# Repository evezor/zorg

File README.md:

# To be named Zorg Placeholder

Zorg is the webportal to the evezor edge systems ecosystem, plus other stuff, I think... maybe

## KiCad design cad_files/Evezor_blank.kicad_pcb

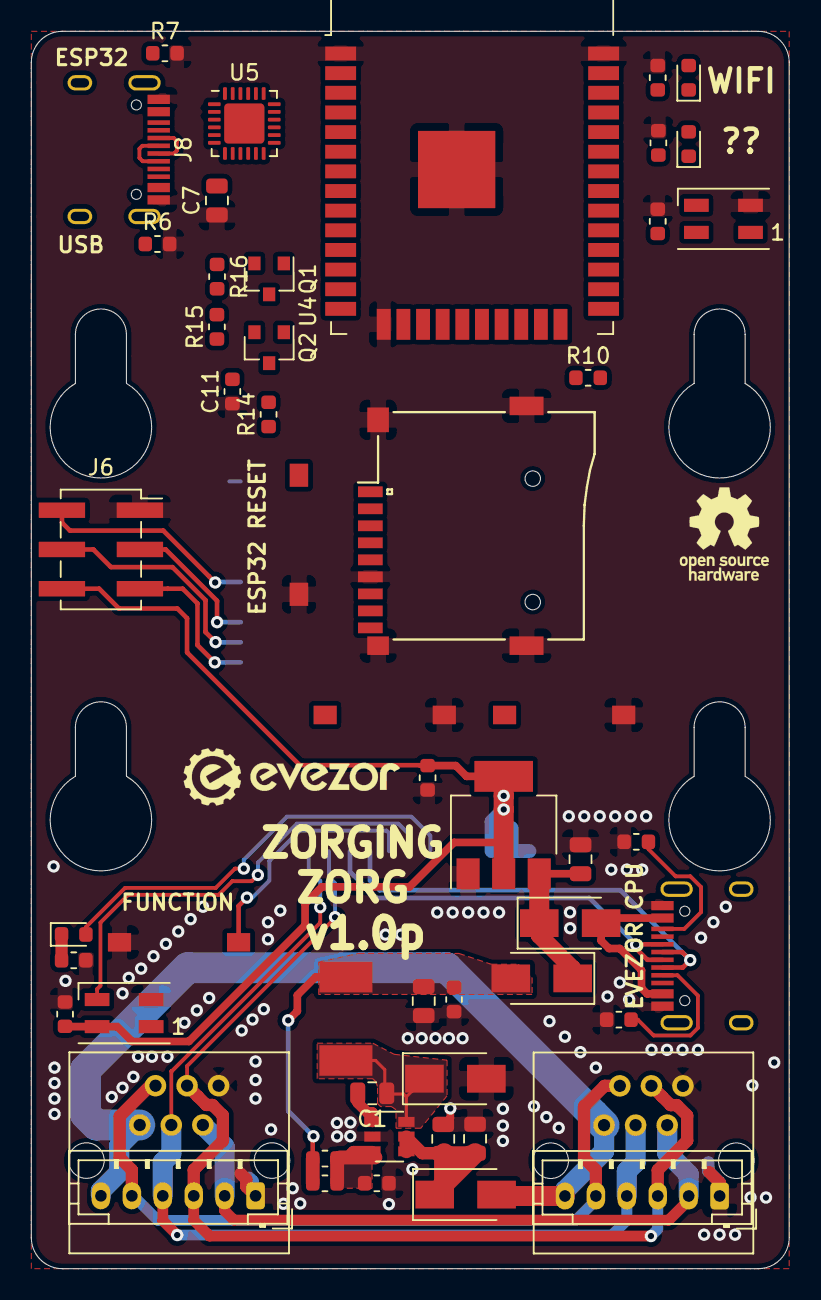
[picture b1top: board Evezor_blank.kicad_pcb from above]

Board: 2 copper layers, 49.0 x 80.0 mm, 54 parts (1 on the bottom side), 50 nets.

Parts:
C1, C3: .1uF 100V; C_0805_2012Metric
C2, C5, C9, C10, C12: .1uF; C_0603_1608Metric
C4: 4.7uF; C_0805_2012Metric
C6: 22uF; C_0805_2012Metric
C7, C8: 10uF; C_0805_2012Metric
C11: 1uF; C_0603_1608Metric
D1, D2, D4, D5: SX35_SCHOTTKY; D_SMA
D3, D7, D8: LED; LED_0603_1608Metric
D6, D9: SK6812MINI; LED_SK6812MINI_PLCC4_3.5x3.5mm_P1.75mm
J1, J8: USB_C_Receptacle_USB2.0; USB_C_Receptacle_HRO_TYPE-C-31-M-12
J2, J3: RJ11; RJ11_C189747_Horizontal
J4, J5: PH; JST_PH_B6B-PH-K_1x06_P2.00mm_Vertical
J6: Conn_02x03_Odd_Even; PinSocket_2x03_P2.54mm_Vertical_SMD
L1: 22uH; INDUCTOR_7.5X6.6_GCDA0630-220MC
Q1, Q2: MMBT2222; SOT-23
R1, R10, R14, R15, R16: 10k; R_0603_1608Metric
R2: 82k; R_0603_1608Metric
R3, R4, R6, R7: 5.1k; R_0603_1608Metric
R5, R17, R18: 15k; R_0603_1608Metric
SW1, SW2, SW3, SW4: SW_Push; SWITCH_2x3_SMD_TACTILE_GREEN
U1: SY8401ABC; SOT-23-6
U2: AMS1117-3.3; SOT-223-3_TabPin2
U3: EDGE_STM32F405_CPU_V1; EDGE_STAMP
U4: ESP32-WROOM-32D; ESP32-WROOM-32
U5: CP2104; QFN-24-1EP_4x4mm_P0.5mm_EP2.6x2.6mm
XS1: uSD-push_push_SMD; Conn_uSDcard

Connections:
+3V3: C7.2, C9.2, C10.1, C12.2, D6.4, D9.4, J6.6, R10.2, R14.2, U2.2, U3.1, U3.18, U4.2, U5.5, U5.6, U5.7, XS1.4
/BOOT: J6.3, U3.36
/CAN_H: J2.3, J3.3, J4.3, J5.3, U3.26
/CAN_L: J2.4, J3.4, J4.4, J5.4, U3.27
/CC1: J1.A5, R4.1
/CC2: J1.B5, R3.1
/CD: U4.27, XS1.9
/D+: J1.A6, J1.B6, U3.25
/D-: J1.A7, J1.B7, U3.24
/DTR: Q1.2, R16.1, U5.23
/ESP_CC1: J8.A5, R7.1
/ESP_CC2: J8.B5, R6.1
/ESP_D+: J8.A6, J8.B6, U5.3
/ESP_D-: J8.A7, J8.B7, U5.4
/ESP_RESET: C11.2, Q2.3, R14.1, SW2.1
/FD_H: J2.2, J3.2, J4.2, J5.2
/FD_L: J2.5, J3.5, J4.5, J5.5
/FUNCTION_BUTTON: SW1.1, U3.23
/HBT_LED: D3.2, U3.21
/HPSI_CLK: U4.13, XS1.5
/HSPI_CS: R10.1, U4.23, XS1.2
/HSPI_MISO: U4.14, XS1.7
/HSPI_MOSI: U4.16, XS1.3
/IO0: Q1.3, U4.25
/NEO_STATUS: D6.3, U3.22
/OLED_SCL: J6.5, U3.34
/OLED_SDA: J6.4, U3.35
/RESET: J6.2, U3.38
/RTS: Q2.2, R15.1, U5.19
/RXD0: U4.34, U5.21
/TXD0: U4.35, U5.20
/USB_VCC: D4.2, J1.A4, J1.A9, J1.B4, J1.B9
/VPSI_CLK: U3.5, U4.30
/VREG_OUT: C2.1, C5.1, C6.1, D5.2, L1.2, R2.1
/VSPI_CS: U3.4, U4.29
/VSPI_MISO: U3.6, U4.31
/VSPI_MOSI: U3.7, U4.37
GND: C3.2, C4.2, C5.2, C6.2, C7.1, C8.2, C9.1, C10.2, C11.1, C12.1, D1.2, D6.2, D9.2, J1.A1, J1.A12, J1.B1, J1.B12, J2.1, J3.1, J4.1, J5.1, J6.1, J8.A1, J8.A12, J8.B1, J8.B12, R1.1, R3.2, R4.2, R5.1, R6.2, R7.2, R17.1, R18.1, SW1.2, SW2.2, SW3.2, SW4.2, U1.2, U2.1, U3.2, U3.17, U3.43, U4.1, U4.15, U4.38, U4.39, U5.2, U5.25, XS1.6
unnamed: C1.1, D1.1, L1.1, U1.6
unnamed: C1.2, U1.1
unnamed: C2.2, R1.2, R2.2, U1.3
unnamed: C3.1, C4.1, D2.1, U1.4, U1.5
unnamed: C8.1, D4.1, D5.1, U2.3
unnamed: D3.1, R5.2
unnamed: D7.1, R17.2
unnamed: D8.1, R18.2
unnamed: J8.A4, J8.A9, J8.B4, J8.B9, U5.8
unnamed: Q1.1, R15.2
unnamed: Q2.1, R16.2
VBUS: D2.2, J2.6, J3.6, J4.6, J5.6

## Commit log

2020-11-29 copy generic pcb files
2020-11-30 add esp/ usb/ status lights and buttons
